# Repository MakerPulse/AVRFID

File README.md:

RPI-RFID
========

This project is ment to be used to scan and process RFID tags for attendance lists or access control.

Source - The code that is loaded onto the actual ID reader
Python_Interface - The GUI interface that is used to manage the attendance system
Circuit - The schematic and layout designes of the circuit board used to read the RFID tags
CaseCad - The CAD files for 3D printing the case for the circuit board

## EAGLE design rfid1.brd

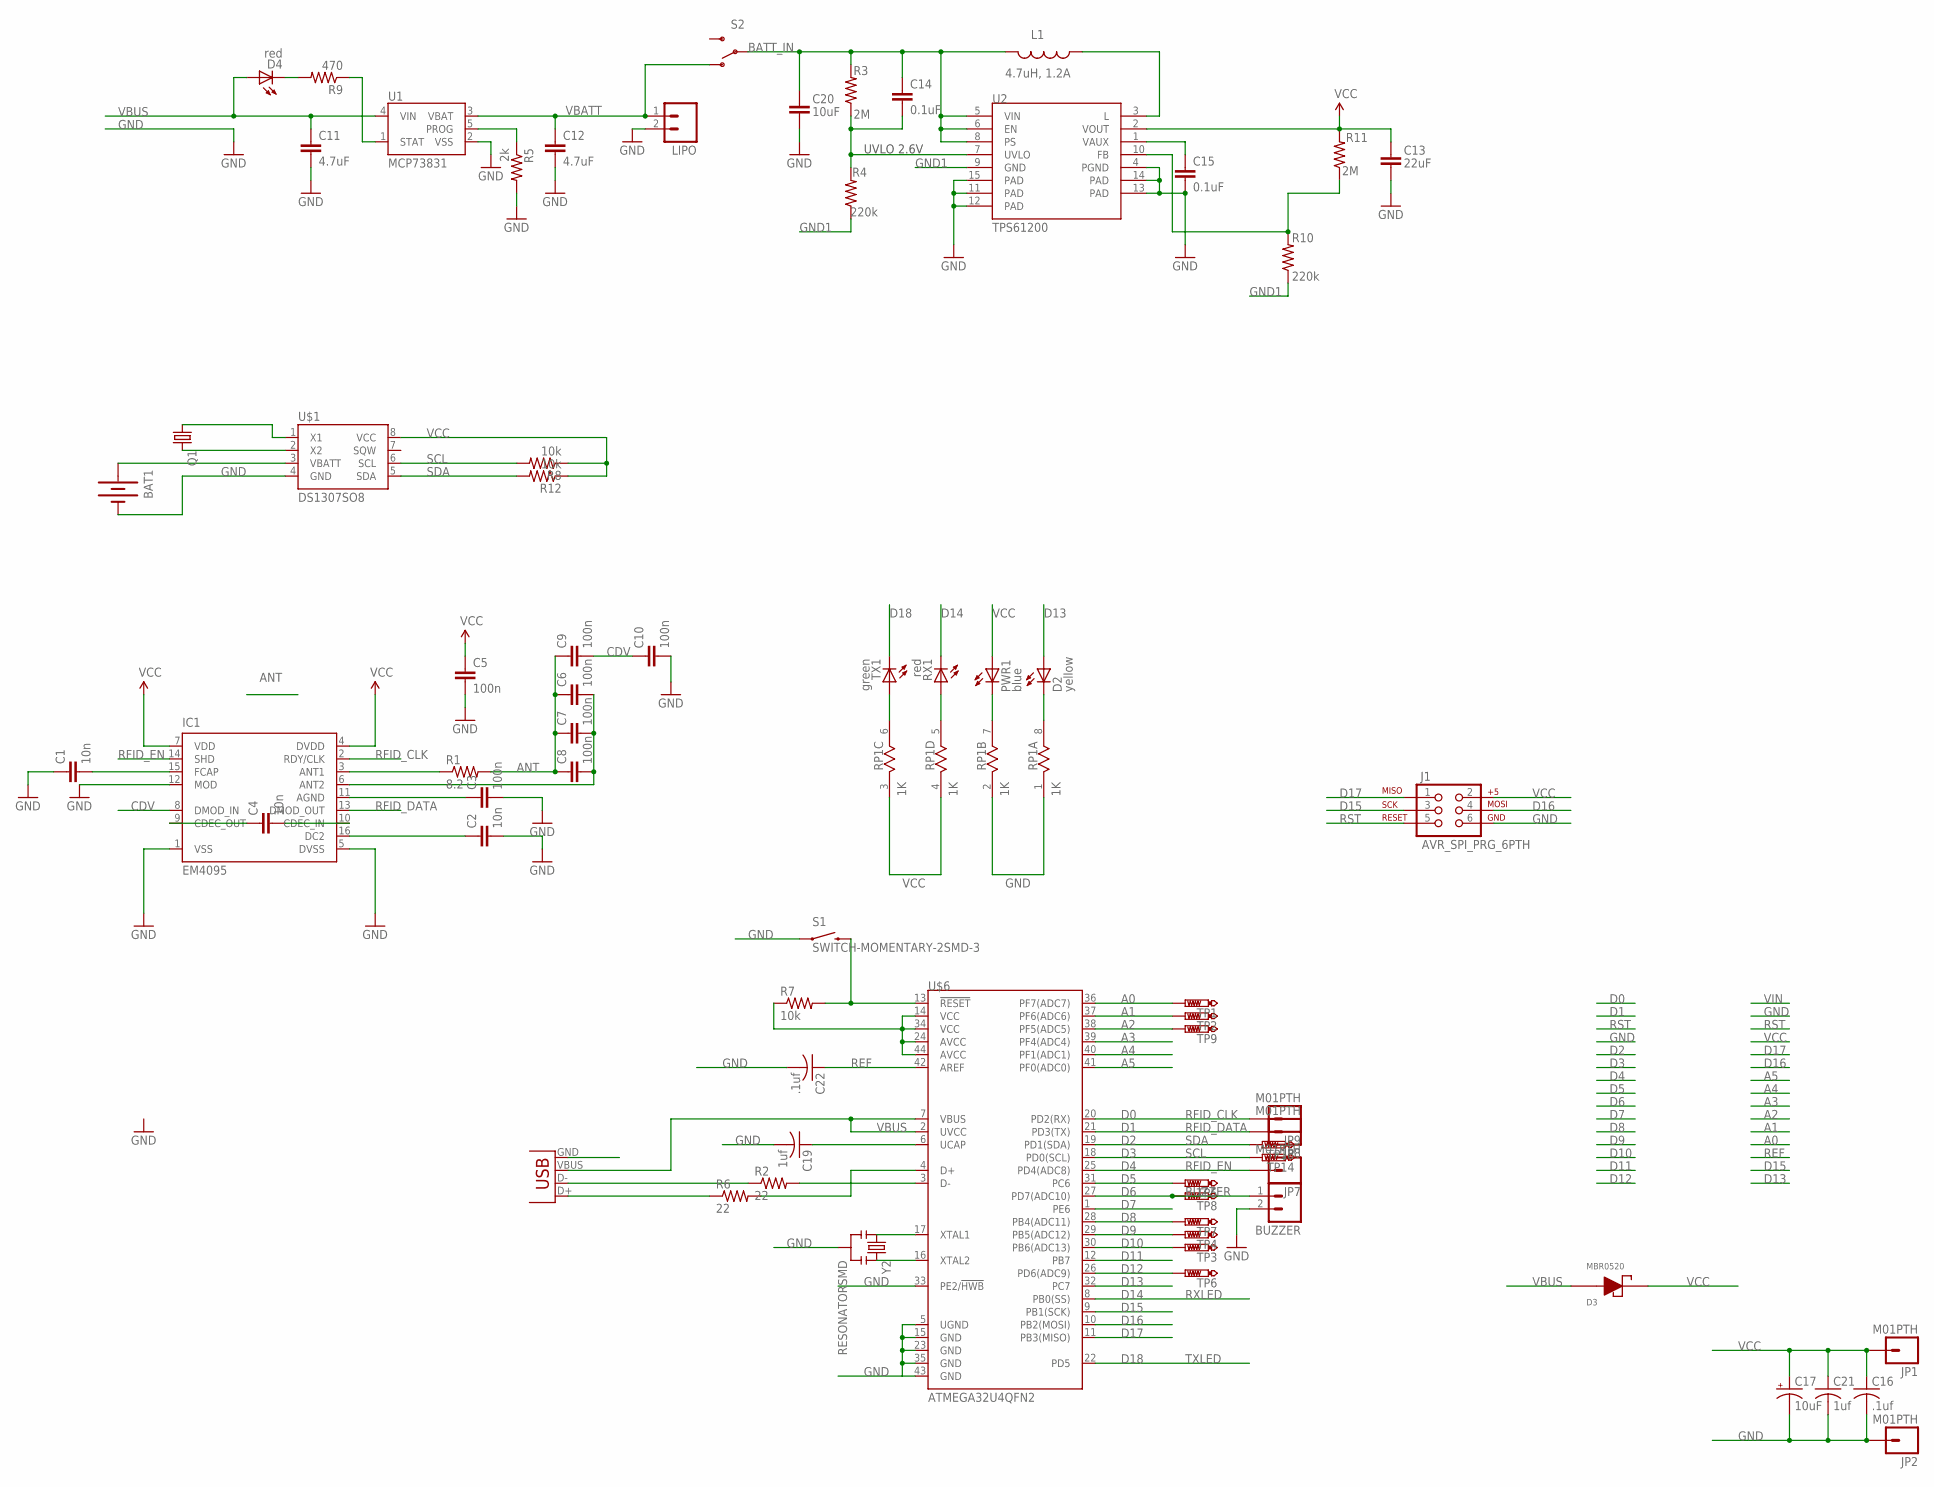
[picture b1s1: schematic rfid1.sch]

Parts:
BAT1: BATTERY12MM; BATTCON_12MM
BUZZER: M02PTH; 1X02
C1, C2, C4: 10n; 0805
C3, C5, C6, C7, C8, C9, C10: 100n; 0805
C11, C12: 4.7uF; 0402-CAP
C13: 22uF; 0805
C14, C15: 0.1uF; 0402-CAP
C16, C22: .1uf; C0603
C17: 10uF; EIA3216
C19, C21: 1uf; C0603
C20: 10uF; 1206
D2: yellow; CHIPLED_0805
D3: MBR0520; SOD-123
D4: red; LED-0603
IC1: EM4095; SO16
J1: AVR_SPI_PRG_6PTH; 2X3
JP1, JP2, JP7, JP8, JP9: M01PTH; 1X01
L1: 4.7uH, 1.2A; CDRH2D09
LIPO: M02PTH; 1X02
PWR1: blue; CHIPLED_0805
Q1: CRYSTALTC26H; TC26H
R1: 8.2; 0805
R2, R6: 22; 0603-RES
R3, R11: 2M; 0402-RES
R4, R10: 220k; 0402-RES
R5: 2k; 0402-RES
R7, R8, R12: 10k; 0603-RES
R9: 470; 0402-RES
RP1: 1K; RES4NT
RX1: red; CHIPLED_0805
S1: SWITCH-MOMENTARY-2SMD-3; TACTILE_SWITCH_SMD-3
S2: SWITCH-SPDTPTH; SWITCH-SPDT
TP1, TP2, TP3, TP4, TP5, TP6, TP7, TP8, TP9, TP13, TP14: PTR1TP15R; TP15R
TX1: green; CHIPLED_0805
U1: MCP73831; SOT23-5
U2: TPS61200; QFN-10_PAD
U$1: DS1307SO8; SO08
U$6: ATMEGA32U4QFN2; QFN-44-NOPAD
X2: USB-MICROB
Y2: RESONATORSMD; RESONATOR-SMD

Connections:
A0: TP1.TP, U$6.36 (PF7(ADC7))
A1: TP2.TP, U$6.37 (PF6(ADC6))
A2: TP9.TP, U$6.38 (PF5(ADC5))
A3: U$6.39 (PF4(ADC4))
A4: U$6.40 (PF1(ADC1))
A5: U$6.41 (PF0(ADC0))
ANT: C6.1, C7.1, C8.1, C9.1, R1.2
BATT_IN: C14.1, C20.1, L1.P$2 (2), R3.2, S2.2, U2.5 (VIN), U2.6 (EN), U2.8 (PS)
CDV: C9.2, C10.1, IC1.8 (DMOD_IN)
D5: TP5.TP, U$6.31 (PC6)
D6: BUZZER.1, TP8.TP, U$6.27 (PD7(ADC10))
D7: U$6.1 (PE6)
D8: TP7.TP, U$6.28 (PB4(ADC11)); also elsewhere on the board
D9: TP4.TP, U$6.29 (PB5(ADC12))
D10: TP3.TP, U$6.30 (PB6(ADC13))
D11: U$6.12 (PB7)
D12: TP6.TP, U$6.26 (PD6(ADC9))
D13: D2.A, U$6.32 (PC7)
D14: RX1.C, U$6.8 (PB0(SS))
D15: J1.3, U$6.9 (PB1(SCK))
D16: J1.4, U$6.10 (PB2(MOSI))
D17: J1.1, U$6.11 (PB3(MISO))
D18: TX1.C, U$6.22 (PD5)
FB: R10.2, R11.1, U2.10 (FB)
GND: BAT1.GND (-), BUZZER.2, C1.1, C2.2, C3.2, C5.2, C10.2, C11.2, C12.2, C13.2, C15.2, C16.2, C17.C (-), C19.2, C20.2, C21.2, C22.2, IC1.1 (VSS), IC1.5 (DVSS), IC1.12 (MOD), J1.6, JP2.1, LIPO.2, R5.2, RP1.1, RP1.2 (1), S1.P$1 (1), U1.2 (VSS), U2.4 (PGND), U2.11 (PAD), U2.12 (PAD), U2.13 (PAD), U2.14 (PAD), U2.15 (PAD), U$1.4 (GND), U$6.5 (UGND), U$6.15 (GND), U$6.23 (GND), U$6.33 (PE2/!HWB), U$6.35 (GND), U$6.43 (GND), X2.GND, Y2.2; also elsewhere on the board
GND1: R4.1, R10.1, U2.9 (GND)
unnamed: IC1.3 (ANT1), R1.1
unnamed 27: D4.C, R9.2; also elsewhere on the board
unnamed: U$6.16 (XTAL2), Y2.3
unnamed: C6.2, C7.2, C8.2, IC1.6 (ANT2)
unnamed: L1.P$1 (1), U2.3 (L)
unnamed: C3.1, IC1.11 (AGND)
unnamed: C4.2, IC1.10 (CDEC_IN)
unnamed: C4.1, IC1.9 (CDEC_OUT)
unnamed: C15.1, U2.1 (VAUX)
unnamed: R5.1, U1.5 (PROG)
unnamed: C2.1, IC1.16 (DC2)
unnamed: R9.1, U1.1 (STAT)
unnamed: C1.2, IC1.15 (FCAP)
unnamed: Q1.1, U$1.1 (X1)
unnamed: U$6.17 (XTAL1), Y2.1
unnamed: Q1.2, U$1.2 (X2)
unnamed: BAT1.PWR@1 (+), U$1.3 (VBATT)
unnamed: R6.2, U$6.4 (D+)
unnamed: R2.2, U$6.3 (D-)
unnamed: C19.1, U$6.6 (UCAP)
unnamed: R2.1, X2.D-
unnamed: R6.1, X2.D+
unnamed: RP1.6 (2), TX1.A
unnamed: RP1.5 (2), RX1.A
unnamed: PWR1.C, RP1.7 (2)
unnamed: D2.C, RP1.8 (2)
REF: C22.1, U$6.42 (AREF)
RFID_CLK: IC1.2 (RDY/CLK), JP9.1, U$6.20 (PD2(RX))
RFID_DATA: IC1.13 (DMOD_OUT), JP8.1, U$6.21 (PD3(TX))
RFID_EN: IC1.14 (SHD), JP7.1, U$6.25 (PD4(ADC8))
RST: J1.5, R7.2, S1.P$2 (2), U$6.13 (!RESET)
SCL: R8.2, TP14.TP, U$1.6 (SCL), U$6.18 (PD0(SCL))
SDA: R12.2, TP13.TP, U$1.5 (SDA), U$6.19 (PD1(SDA))
UVLO: C14.2, R3.1, R4.2, U2.7 (UVLO)
VBATT: C12.1, LIPO.1, S2.1 (O), U1.3 (VBAT)
VBUS: C11.1, D3.2 (AN), D4.A, U1.4 (VIN), U$6.2 (UVCC), U$6.7 (VBUS), X2.VBUS; also elsewhere on the board
VCC: C5.1, C13.1, C16.1, C17.A (+), C21.1, D3.1 (CA), IC1.4 (DVDD), IC1.7 (VDD), J1.2, JP1.1, PWR1.A, R7.1, R8.1, R11.2, R12.1, RP1.3 (1), RP1.4 (1), U2.2 (VOUT), U$1.8 (VCC), U$6.14 (VCC), U$6.24 (AVCC), U$6.34 (VCC), U$6.44 (AVCC)

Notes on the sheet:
RXLED
TXLED
UVLO 2.6V
BUZZER

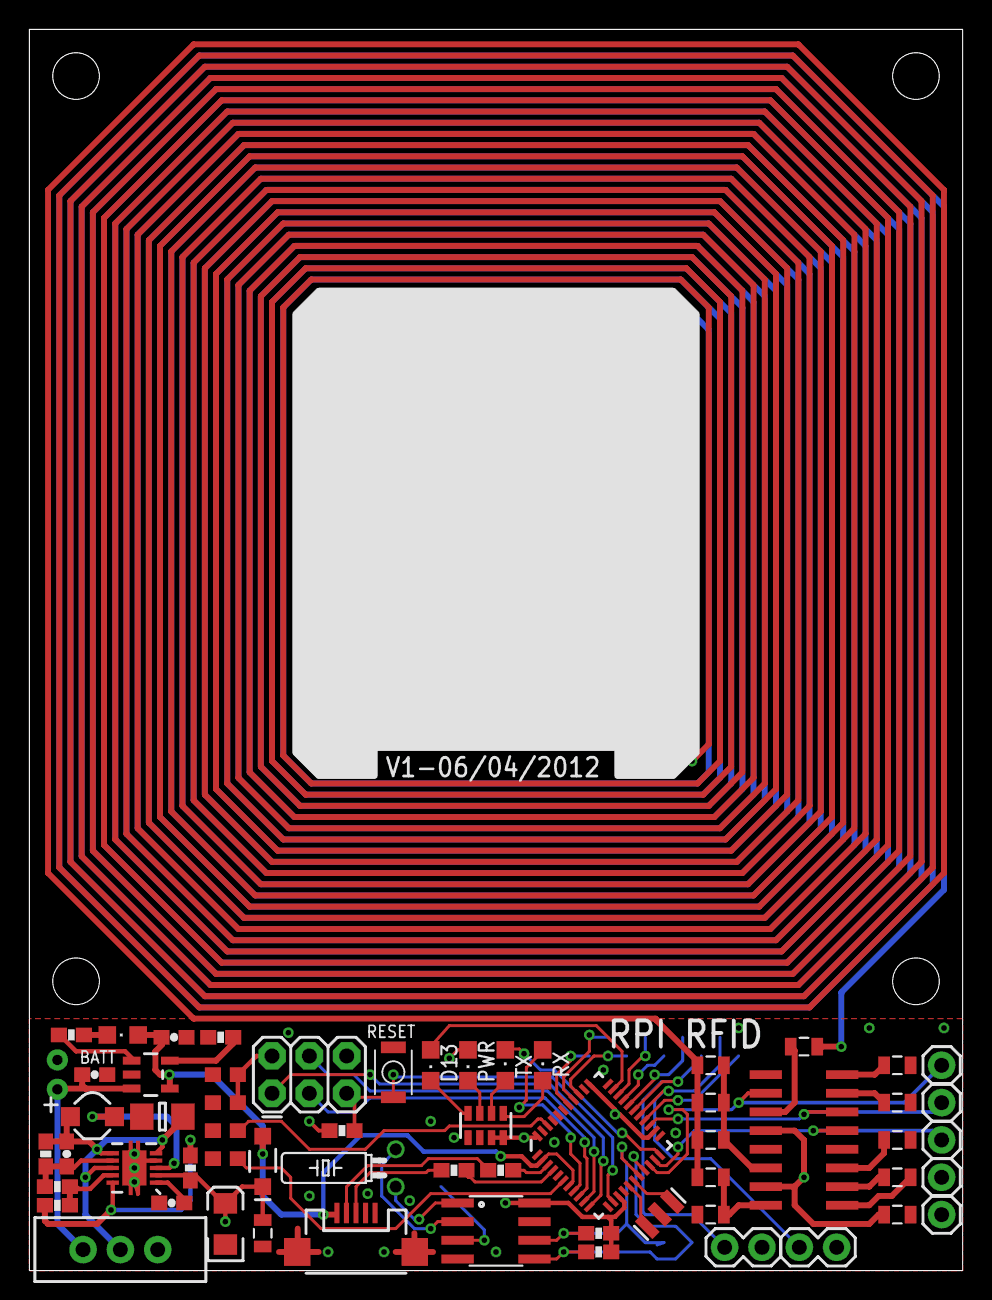
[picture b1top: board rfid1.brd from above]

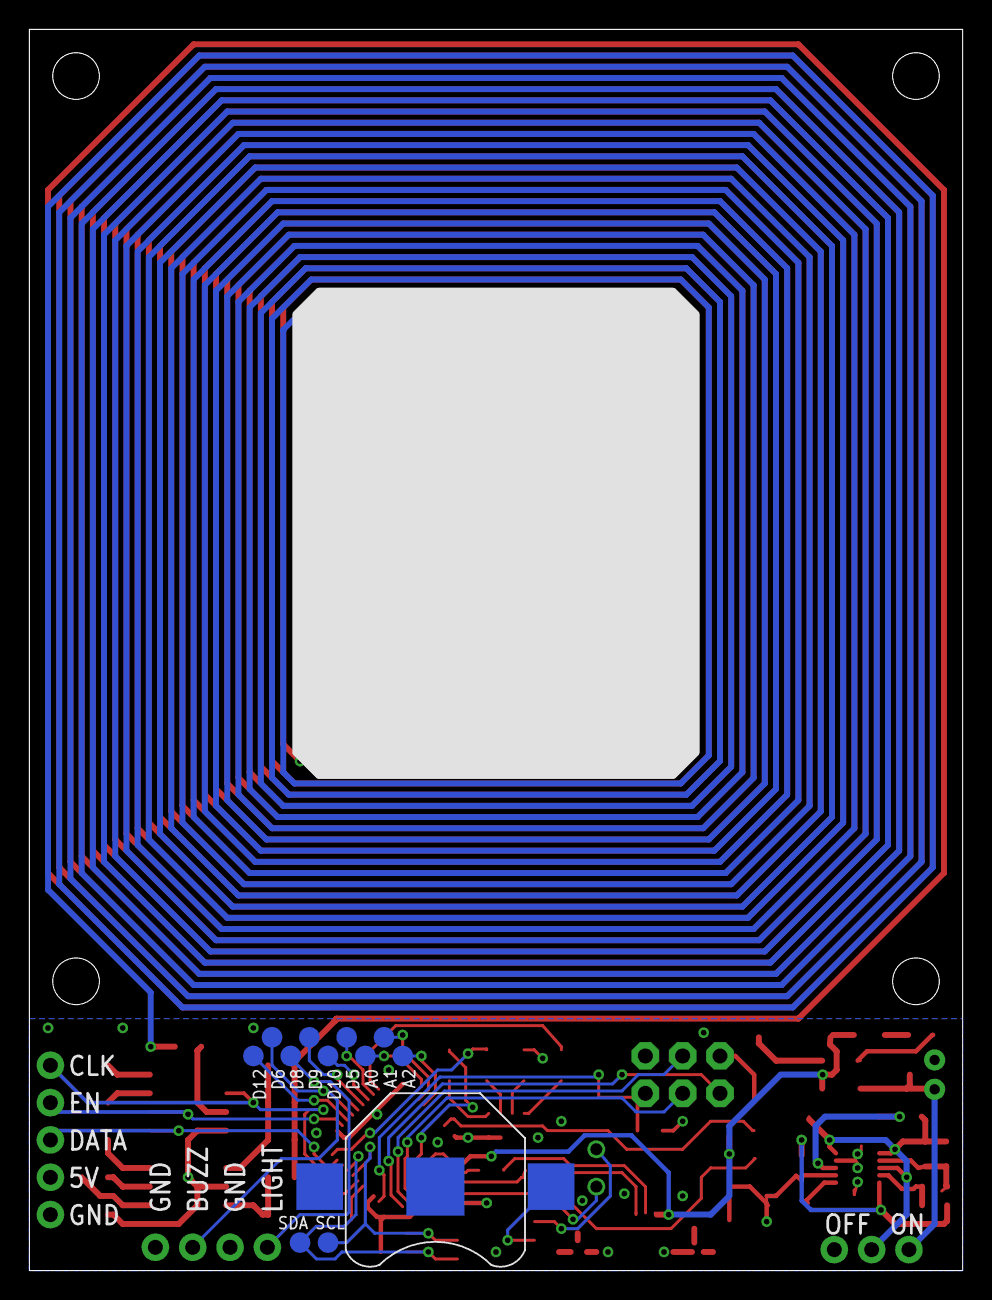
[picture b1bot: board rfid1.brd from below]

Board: 2 copper layers, 63.5 x 84.5 mm, 72 parts (13 on the bottom side), 58 nets.

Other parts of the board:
CHARGE: RED; CHIPLED_0805
LIGHT: 1X02

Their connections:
D8: LIGHT.1; also elsewhere on the board
GND: LIGHT.2; also elsewhere on the board
unnamed 27: CHARGE.C; also elsewhere on the board
VBUS: CHARGE.A; also elsewhere on the board

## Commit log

2012-05-31 First RCOS commit - RFID reader board and schematic with RFID chip, microcontroller, real time clock, USB LiPO charger, and boost converter.
2012-06-08 Updated part sizes and added acces pads for unused avr pins. Added silk labels and free area. Revision sent for manufacturing 6/4/12
2012-06-23 Cad files for a case holding reader, battery, leds
2012-07-14 created the source code and included the unported avrfid code
2012-07-14 removed compile errors, now to begin to port the pinmappings over to arduino
2012-07-14 split up the main function into the two arduino functions
2012-07-14 fixed a couple of declaration bugs
2012-07-14 removed the check whitelist functions, sucessfull build
2012-07-14 removed the last whitelist line and removed some servo init lines
2012-07-14 realized that the avrfid only uses the timers for the servos, got rid of them
2012-07-14 removed the function to add a list of whitelisted names, as a whitelist is not used anymore
2012-07-14 tried to switch the interrupts to arduino, did not work
2012-07-15 getting the interrupts to work is hard
2012-07-15 got the interrupts to work, slight problems with some serial ports going missing though
2012-07-15 I was reading from the wrong pin, pin 2 is actualy 0x04 not 0x02
2012-07-18 swapped out the actual array type for a defined type
2012-07-19 One number, one tiny little ittybity mini number. 9 hours of work wasted because it was wrong. Two people did not find it either.
2012-07-19 debugging the multibit and count to multibit conversion functions
2012-07-19 board can read cards, still needs some tweaking to solve some read errors, and a glitch where the serial port freezes
2012-07-29 removed the debug print statements, ids scan much faster now
2012-09-21 created gui application in processing. Doesnt save or read rfids yet. opens file, lists names, adds names, opens serial port, search works
2012-09-22 created serial search function
2012-09-22 added rfid search, will add unknown entires
2012-09-22 fixed slowness after opening serial port
2012-09-23 added mark button and present attribute
2012-09-24 added file saving capability
2012-09-24 added function to save rfid list on exit, mark new entries as present
2012-09-24 highlighted current entry, bug fixes and tweaks, see instructions
2012-09-24 built applications for all OS
2012-10-13 changed 9 from a 0 value to a gray value (previous bits value)
2012-10-13 fixed bug when opening and saving files, top name would be deleted
2012-10-20 made the output just display hex, and made an led blink when a card is read
2012-10-20 messing with some causes of the serial freezing
2012-10-20 fixed a problem with the delay function not working because all interrupts were disabled
2012-10-21 minor updates
2012-11-26 created a basic program to begin reading tags using samplecode
2012-11-27 changed the read to a non-blocking read so that the child thread will quit when the parent does
2012-11-29 added comments to the functions and classes
2012-11-29 UI now correctly reads tags
2012-11-29 added a new button for connecting the RFID reader
2012-11-29 started creating the buttons for interacting with the program
2012-11-29 added temporary icons
2012-12-01 added new buttons that do not do anything yet
2012-12-01 fixed the partial tag read function
2012-12-01 modified the comment for the main qt window
2012-12-01 updated the new person widget and changed the way the program is closed
2012-12-01 re added the timeout, realized it was only working smoothly becasue fake data was being sent to it
2012-12-01 adding buttons to the add user box
2012-12-01 added a warning message to prevent the close button from accadentaly being hit
2012-12-01 centered the new person popup window
2012-12-01 added a license and some more comments for the functions
2012-12-01 changed the add user window to look more fluid and allow resizing
2012-12-01 updated window titles
2012-12-02 added a box for searching the name list
2012-12-02 added a fake database and began to create a search function
2012-12-02 added a functional person search, may need to be optimized in the future
2012-12-02 tweeked the search and the database slightly to standardize it
2012-12-03 moved where the the search function is located to make more sense and to be more compact
2012-12-03 made the search case insensitive
2012-12-04 adding new users and rfid tags now works
2012-12-13 added support for detecting when a divice is plugged into the computer, beginning to use it to auto detect arduinos
2012-12-13 program now automaticly spawns a new thread for each new divice attached to the computer
2012-12-17 removed some debug cluttering output
2012-12-17 addded error catching to try to debug the program on windows
2012-12-17 added a line to detect if the threading library is breaking
2012-12-17 removed the debug line to prevent it from clashing with threads debug messages
2012-12-17 removed the threads to see what the serial library is doing on windows
2012-12-17 removed new port notifications
2012-12-17 debug messaging to print all of the ports attached
2012-12-17 more debug messages to figure out why python is not finishing the periodicly called function
2012-12-17 added one more line to see what is going on
2012-12-17 even more debugging messages for the serial finding
2012-12-17 added a length of the current ports to be displayed durring the function
2012-12-17 turned the generator object into a list
2013-01-22 commented a function
2013-01-22 updating the method of storing tags from appending the data to the view to appending it to a list that can be updated
2013-01-22 updated the method of displaying the tags, if a tag is in the database it will display as the users name instead
2013-01-22 removed the connect rfid reader button as the reader will connect automaticly
2013-01-22 updating the interface buttons to save and load the attendance sheets
2013-01-22 added functionality for creating a new attendance sheet and made the tag list view more responsive to modification
2013-01-22 added saving and loading features for the tag list
2013-01-22 added feature to save database when a new tag-person relation is added
2013-04-05 disabled serial during the reading from the antenna interrrupt
2013-04-07 fixed a frezing error caused by an out of bounds error
2013-04-07 removed the extra serial print functions, added printout for id tag
2013-04-07 Moved the circuit board schematics into their own folder
2013-04-07 removed the old serial interface program
2013-04-07 renamed the cad folder to CaseCad
2013-04-07 Added folder structure descriptions to the README file
2013-04-08 added feature to add users by double clicking on unknown tags
2013-04-08 fixed probelm with passing wrong view into new user widget
2013-04-09 added the ability to play sound on card read (badly)
2013-04-09 changed notifaction noise code to play in a thread instead of blocking
2013-04-09 put the actual date in the filename instead of text stating todaysdate
2013-04-11 reversed the order of the attendance list so new tags apear on the top of the list
2013-04-16 Added comments to the functions to begin cleanup of the code
2013-04-16 added a gitignore
2013-04-22 added an array to define what kind of metadata should be present in the new user field fixes #5
2013-04-22 updated the icon set and organized the icon locations
2013-04-22 fixed a bug where program crashes if the database is not present
2013-04-22 removed extra unnessasary files from the python interface
2013-04-22 updated the notification noise
2013-06-26 converted tabs to spaces in the python interface
2013-06-26 changed majority of code to conform with pep8
2013-06-26 fixed error wiht calling IDRelation before initilizing it
2013-06-26 begining to add more user control over program operation
2013-06-26 added basic ability to edit tags info in the database
2013-06-26 added checked and unchecked icons for reader connectivity
2013-06-26 re enabled RFID box for new tag items
2013-06-26 updated edit ability to allow for editing from the currently scanned tags
2013-06-27 moved the new person widget to its own file
2013-06-27 added a template for a about page
2013-06-27 added .pyc files to the git ignore list
2013-06-27 added a about page to the python client
2013-06-27 added menu options for all currently planned features
2013-06-27 added possible but untested serial enumeration methods for windows and OSX
2013-06-27 added the ctrl+c interrupt to kill the program
2013-06-27 added ttyACM to the list of serial connections to look for
2013-06-27 added a second message passing interface to the threaded tasks
2013-06-28 started working on better exception handling for connections
2013-06-28 finished error catching for the time being
2013-06-28 created a list of currently open serial ports to be used with the menu
2013-06-28 currently active serial ports are displayed on the connection menu
2013-06-28 can now manually connect to serial ports from the reader menu
2013-06-28 added method to disconnect manually from a serial port
2013-06-28 removed the possibility of multiple databases on a single computer
2013-06-28 added safety close check for modified attendance documents
2013-06-28 Added version number to about screen
2013-06-28 Disabled all of the un-implemented menu bar options
2013-07-01 fixed a few dumb pyadio mistakes
2013-07-01 fixed a forgotten stream close
2013-07-01 fixed a quit bug
2013-07-01 fixed a mistake from a refactor
2013-07-16 Add #!

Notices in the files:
parts and their libraries:
SparkFun-Aesthetics: Licensing: CC v3.0 Share-Alike You are welcome to use this library for commercial purposes.
